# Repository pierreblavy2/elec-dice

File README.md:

# elec-dice

# Introduction
This project is an electronic dice that allow to launch 3D4, 3D6, 3D8, 3D10, 1D12, 1D20 or to compute the sum of launched dices. This project was designed to used common and cheap electronic components.

# Components
|quantity|reference|desciption|datasheet|
|---|---|---|---|
|1| 2468|2xAAA battery case|https://www.mouser.fr/datasheet/2/215/468-741064.pdf|
|3|05611AH|7 digit+decimal, common cathode, 0.56 inches|http://www.wayjun.com/Datasheet/Led/Segment%20Digit%20LED%20Display.pdf|
|4|74HC595|8bits shift register,DIP16|https://www.ti.com/lit/ds/symlink/sn74hc595.pdf|
|4|DIP16 support|
|1|ATTiny85|DIP8|https://ww1.microchip.com/downloads/en/DeviceDoc/Atmel-2586-AVR-8-bit-Microcontroller-ATtiny25-ATtiny45-ATtiny85_Datasheet.pdf|
|1|DIP8 support||
|1|5V step up|(1)||
|24|330 ohms|Axial resistor, 1/4W (2)|
|1 |10k ohms|Axial resistor, 1/4W (3)|
|8|1n4007|Diode (4)|https://www.vishay.com/docs/88503/1n4001.pdf|
|8||6x6mm push button|https://www.hdk.co.jp/pdf/eng/e291702.pdf|
|1|ADD3|RPG book, a good dungeon master, friends|

(1) This component is not referenced properly, I've found mine here 
https://www.aliexpress.com/item/32789971588.html but any pin compatible 5V step up will
do the trick. The PCB was designed with extra space arount the 5V step up module, so you can
easily edit it to use an other kind of module. 
The module looks like [this](https://github.com/pierreblavy2/elec-dice/blob/main/doc/5V_OSJK.png?raw=true).

(2) The 330 Ohms resistors are used to protect the 05611AH diodes. You must choose their value according to the kind of led you're using, and the desired brightness. The formula is R=(5-Vf)/If. Vf is the forward voltage of a single LCD segment, If is the segment forward intensity. Note that you must choose a value that's BIGGER than the one you've just computed.

(3) This resistor is used as a pulldown for switches, a wide range of values between 1K to 20K does the job.

(4) These diodes are used to protect the 74hc595 when we press more than one switch. The diode forward voltage drop must be lower than 2V in order to have sufficient voltage on the ATTiny85 input pin.

# Pictures

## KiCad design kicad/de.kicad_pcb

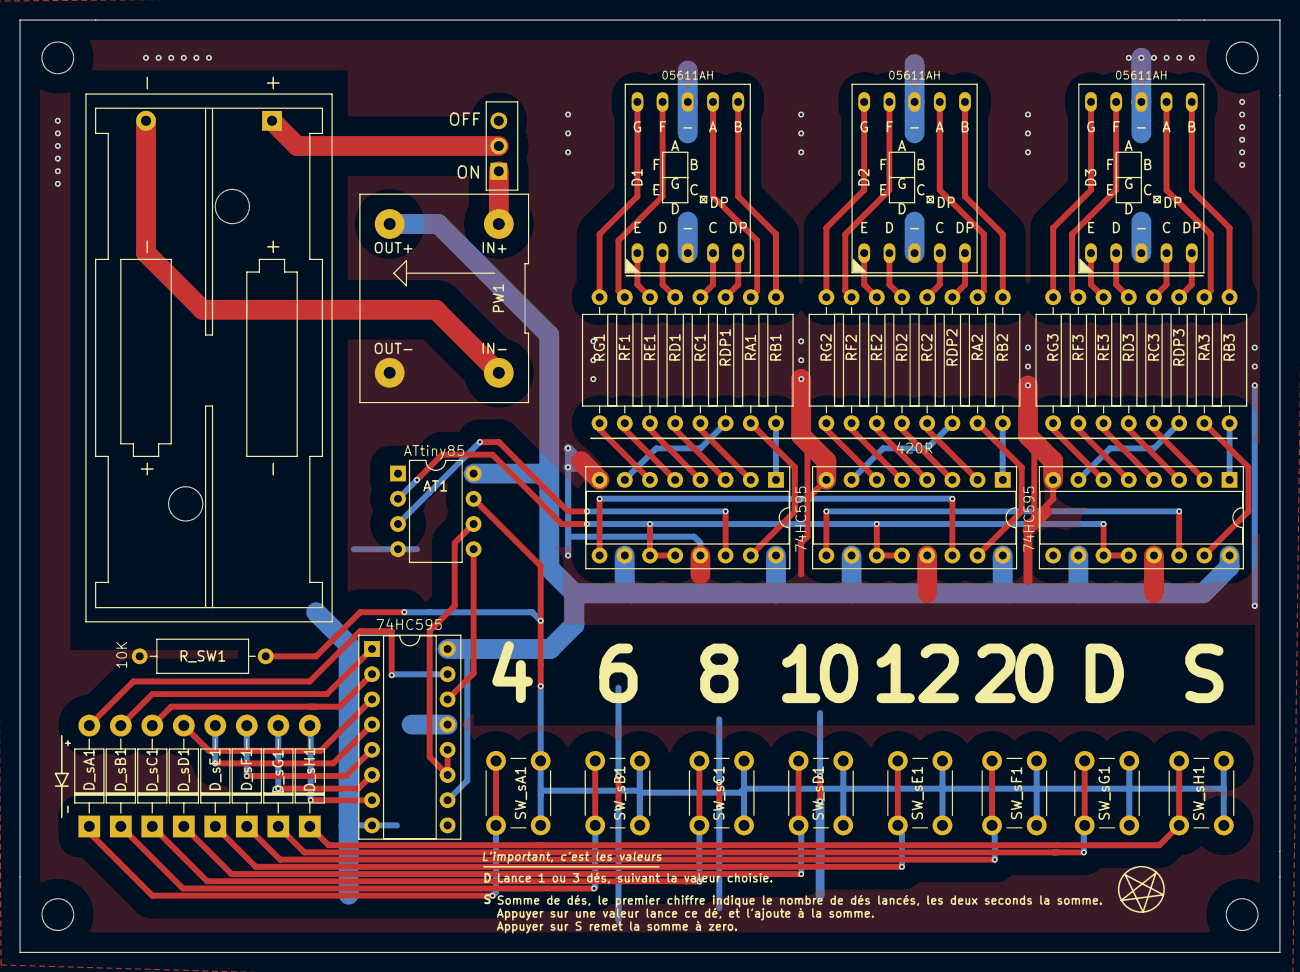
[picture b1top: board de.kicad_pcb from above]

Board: 4 copper layers, 127.0 x 94.0 mm, 52 parts (0 on the bottom side), 76 nets.

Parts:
AT1: ATtiny85-20PU; DIP-8_W7.62mm
BT1: Battery; BatteryHolder_Keystone_2468_2xAAA
D1, D2, D3: 05611AH; 7segments-05611AH
D_sA1: D; D_DO-41_SOD81_P10.16mm_Horizontal
D_sB1: D; D_DO-41_SOD81_P10.16mm_Horizontal
D_sC1: D; D_DO-41_SOD81_P10.16mm_Horizontal
D_sD1: D; D_DO-41_SOD81_P10.16mm_Horizontal
D_sE1: D; D_DO-41_SOD81_P10.16mm_Horizontal
D_sF1: D; D_DO-41_SOD81_P10.16mm_Horizontal
D_sG1: D; D_DO-41_SOD81_P10.16mm_Horizontal
D_sH1: D; D_DO-41_SOD81_P10.16mm_Horizontal
PW1: 5V_OSJK
RA1, RA2, RA3: 330; R_Axial_DIN0309_L9.0mm_D3.2mm_P12.70mm_Horizontal
RB1, RB2, RB3: 330; R_Axial_DIN0309_L9.0mm_D3.2mm_P12.70mm_Horizontal
RC1, RC2, RC3: 330; R_Axial_DIN0309_L9.0mm_D3.2mm_P12.70mm_Horizontal
RD1, RD2, RD3: 330; R_Axial_DIN0309_L9.0mm_D3.2mm_P12.70mm_Horizontal
RDP1, RDP2, RDP3: 330; R_Axial_DIN0309_L9.0mm_D3.2mm_P12.70mm_Horizontal
RE1, RE2, RE3: 330; R_Axial_DIN0309_L9.0mm_D3.2mm_P12.70mm_Horizontal
RF1, RF2, RF3: 330; R_Axial_DIN0309_L9.0mm_D3.2mm_P12.70mm_Horizontal
RG1, RG2, RG3: 330; R_Axial_DIN0309_L9.0mm_D3.2mm_P12.70mm_Horizontal
R_SW1: 10K; R_Axial_DIN0309_L9.0mm_D3.2mm_P12.70mm_Horizontal
SW_sA1: SW_Push; SW_PUSH_6mm_H5mm
SW_sB1: SW_Push; SW_PUSH_6mm_H5mm
SW_sC1: SW_Push; SW_PUSH_6mm_H5mm
SW_sD1: SW_Push; SW_PUSH_6mm_H5mm
SW_sE1: SW_Push; SW_PUSH_6mm_H5mm
SW_sF1: SW_Push; SW_PUSH_6mm_H5mm
SW_sG1: SW_Push; SW_PUSH_6mm_H5mm
SW_sH1: SW_Push; SW_PUSH_6mm_H5mm
S_PW1: SW_SPDT; PinHeader_1x03_P2.54mm_Horizontal
UD_2: 74HC595; DIP-16_W7.62mm_Socket
U_D1, U_D3: 74HC595; DIP-16_W7.62mm_Socket
U_SW1: 74HC595; DIP-16_W7.62mm_Socket

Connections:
+5V: AT1.8, PW1.2, UD_2.10, UD_2.16, U_D1.10, U_D1.16, U_D3.10, U_D3.16, U_SW1.10, U_SW1.16
/D_clocks: AT1.2, UD_2.11, UD_2.12, U_D1.11, U_D1.12, U_D3.11, U_D3.12
/D_data: AT1.3, U_D1.14
/Digit 2/data_in: UD_2.14, U_D1.9
/Digit 3/data_in: UD_2.9, U_D3.14
/S_clocks: AT1.6, U_SW1.11, U_SW1.12
/S_data: AT1.5, U_SW1.14
/S_switch: AT1.7, R_SW1.1, SW_sA1.2, SW_sB1.2, SW_sC1.2, SW_sD1.2, SW_sE1.2, SW_sF1.2, SW_sG1.2, SW_sH1.2
GND: AT1.4, D1.3, D1.8, D2.3, D2.8, D3.3, D3.8, PW1.3, R_SW1.2, UD_2.8, UD_2.13, U_D1.8, U_D1.13, U_D3.8, U_D3.13, U_SW1.8, U_SW1.13
unnamed: BT1.1, S_PW1.2
unnamed: BT1.2, PW1.4
unnamed: D1.1, RE1.1
unnamed: D1.2, RD1.1
unnamed: D1.4, RC1.1
unnamed: D1.5, RDP1.1
unnamed: D1.6, RB1.1
unnamed: D1.7, RA1.1
unnamed: D1.9, RF1.1
unnamed: D1.10, RG1.1
unnamed: D2.1, RE2.1
unnamed: D2.2, RD2.1
unnamed: D2.4, RC2.1
unnamed: D2.5, RDP2.1
unnamed: D2.6, RB2.1
unnamed: D2.7, RA2.1
unnamed: D2.9, RF2.1
unnamed: D2.10, RG2.1
unnamed: D3.1, RE3.1
unnamed: D3.2, RD3.1
unnamed: D3.4, RC3.1
unnamed: D3.5, RDP3.1
unnamed: D3.6, RB3.1
unnamed: D3.7, RA3.1
unnamed: D3.9, RF3.1
unnamed: D3.10, RG3.1
unnamed: D_sA1.1, SW_sA1.1
unnamed: D_sA1.2, U_SW1.15
unnamed: D_sB1.1, SW_sB1.1
unnamed: D_sB1.2, U_SW1.1
unnamed: D_sC1.1, SW_sC1.1
unnamed: D_sC1.2, U_SW1.2
unnamed: D_sD1.1, SW_sD1.1
unnamed: D_sD1.2, U_SW1.3
unnamed: D_sE1.1, SW_sE1.1
unnamed: D_sE1.2, U_SW1.4
unnamed: D_sF1.1, SW_sF1.1
unnamed: D_sF1.2, U_SW1.5
unnamed: D_sG1.1, SW_sG1.1
unnamed: D_sG1.2, U_SW1.6
unnamed: D_sH1.1, SW_sH1.1
unnamed: D_sH1.2, U_SW1.7
unnamed: PW1.1, S_PW1.1
unnamed: RA1.2, U_D1.15
unnamed: RA2.2, UD_2.15
unnamed: RA3.2, U_D3.15
unnamed: RB1.2, U_D1.1
unnamed: RB2.2, UD_2.1
unnamed: RB3.2, U_D3.1
unnamed: RC1.2, U_D1.2
unnamed: RC2.2, UD_2.2
unnamed: RC3.2, U_D3.2
unnamed: RD1.2, U_D1.3
unnamed: RD2.2, UD_2.3
unnamed: RD3.2, U_D3.3
unnamed: RDP1.2, U_D1.7
unnamed: RDP2.2, UD_2.7
unnamed: RDP3.2, U_D3.7
unnamed: RE1.2, U_D1.4
unnamed: RE2.2, UD_2.4
unnamed: RE3.2, U_D3.4
unnamed: RF1.2, U_D1.5
unnamed: RF2.2, UD_2.5
unnamed: RF3.2, U_D3.5
unnamed: RG1.2, U_D1.6
unnamed: RG2.2, UD_2.6
unnamed: RG3.2, U_D3.6

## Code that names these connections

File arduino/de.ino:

//ATTiny85
//processor ATTiny85
//clock internal 16MHz
//programmer Arduino as ISP (not arduinoISP)

//--- wires ---
//Switches
#define S_DATA     ATTINY85_PIN5
#define S_CLOCKS   ATTINY85_PIN6
#define S_SWITCHES ATTINY85_PIN7

//LED
#define D_DATA   ATTINY85_PIN3
#define D_CLOCKS ATTINY85_PIN2


//--- program modes ---
//Modes
#define MODE_DICE true
#define MODE_SUM  false
#include "attiny85.hpp"
#include "display.hpp"
#include "digit_to_byte.hpp"
#include "input.hpp"
#include "dice.hpp"


Display<3>   display(D_DATA , D_CLOCKS) ;
Input<1>     input  (S_DATA , S_CLOCKS , S_SWITCHES);
byte         last_input;
Dice         dice;

bool dice_mode = MODE_DICE;
byte dice_sum;
byte dice_num;




void anime(){
  byte x=0b00000001;
  for(size_t i = 0; i < 8; ++i){
    display.set_byte<0>(x);
    display.set_byte<1>(x);
    display.set_byte<2>(x); 
    display.update();
    delay(50);
    x<<=1;
  }
}



void display_number(byte r){
  display.set_byte<0>(digit_to_byte(r%10,false));
  display.set_byte<1>(digit_to_byte(r/10,false));
  display.set_byte<2>(digit_to_byte(0b00000000,false));
}

void update_dice_sum(byte x){
  if(dice_num<9){
    ++dice_num;
    dice_sum+=x;
  }
  display_number(dice_sum);
  display.set_byte<2>(digit_to_byte(dice_num,true));
}



//input callbacks : One dice per digit
template<int D>
void digit_1_dice_t(){
  anime();
  
  if(dice_mode == MODE_DICE){
      display.set_byte<0>(digit_to_byte(dice(D)%10,true));
      display.set_byte<1>(digit_to_byte(dice(D)%10,true));
      display.set_byte<2>(digit_to_byte(dice(D)%10,true));
  }
  else{
    update_dice_sum(dice(D));
  }
  display.update();
}

void on_d4() {digit_1_dice_t<4>();}
void on_d6() {digit_1_dice_t<6>();}
void on_d8() {digit_1_dice_t<8>();}
void on_d10(){digit_1_dice_t<10>();}


//input callbacks : One dice per 2 digit
template<int D>
void digit_2_dice_t(){
   anime();
   auto r = dice(D);
  
  if(dice_mode == MODE_DICE){
      display.set_byte<0>(digit_to_byte(r%10,false));
      display.set_byte<1>(digit_to_byte((r/10)%10 ,false));
      display.set_byte<2>(0b00000000);
  }
  else{
    update_dice_sum(dice(D));
  }
  display.update();
}


void on_d12() {digit_2_dice_t<12>();}
void on_d20() {digit_2_dice_t<20>();}


void on_sum(){
  dice_mode = MODE_SUM;
  dice_num = 0;
  dice_sum = 0;
  display.set_byte<0>(digit_to_byte(0));
  display.set_byte<1>(digit_to_byte(0));
  display.set_byte<2>(digit_to_byte(0));
  display.update();
}

void on_dice(){
  dice_mode = MODE_DICE;
  display.set_byte<0>(0);
  display.set_byte<1>(0);
  display.set_byte<2>(0);
  display.update();
}



void setup() {
  pinMode(S_DATA    ,OUTPUT);  digitalWrite(S_DATA    ,LOW);
  pinMode(S_CLOCKS  ,OUTPUT);  digitalWrite(S_CLOCKS  ,LOW);
  pinMode(S_SWITCHES,INPUT);   digitalWrite(S_SWITCHES,LOW);
  pinMode(D_CLOCKS  ,OUTPUT);  digitalWrite(D_CLOCKS  ,LOW);
  pinMode(D_DATA    ,OUTPUT);  digitalWrite(D_DATA    ,LOW);
  delay(250);
  
  input.init(); //should flush 0 to switches
  
  //attach callbacks to input
  /*
  input.register_rise(0,on_d4);
  input.register_rise(1,on_d6);
  input.register_rise(2,on_d8);
  input.register_rise(3,on_d10);
  input.register_rise(4,on_d12);
  input.register_rise(5,on_d20);
  input.register_rise(6,on_dice_sum);
  input.register_rise(7,on_dice);
  */

  display.set_byte<0>(0b10101010);
  display.set_byte<1>(0b01010101);
  display.set_byte<2>(0b11001100);
  display.update_force();
  delay(700);

  input.scan();
  last_input=input.data[0];
  
}



void loop() {
  byte mask;


  
  //track changes
  input.scan();
  mask = 0b10000000;
  
  for(size_t i=0; i < 8; ++i){
    byte old_bit = mask & last_input;
    byte new_bit = mask & input.data[0];
    if(old_bit!=new_bit){
    bool is_rise = (old_bit==0);
    if(is_rise){
      switch(i){
        case 0 : {on_d4();   break;}
        case 1 : {on_d6();   break;}
        case 2 : {on_d8();   break;}
        case 3 : {on_d10();  break;}
        case 4 : {on_d12();  break;}
        case 5 : {on_d20();  break;}
        case 6 : {on_dice(); break;}
        case 7 : {on_sum();  break;}
      }
    }
    }
    mask>>=1;
  }
  last_input=input.data[0];

  
  display.update();
}
